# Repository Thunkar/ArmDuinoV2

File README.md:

# ArmDuinoV2
Second version of the robotic arm. Now including hardware, software and (some) documentation.

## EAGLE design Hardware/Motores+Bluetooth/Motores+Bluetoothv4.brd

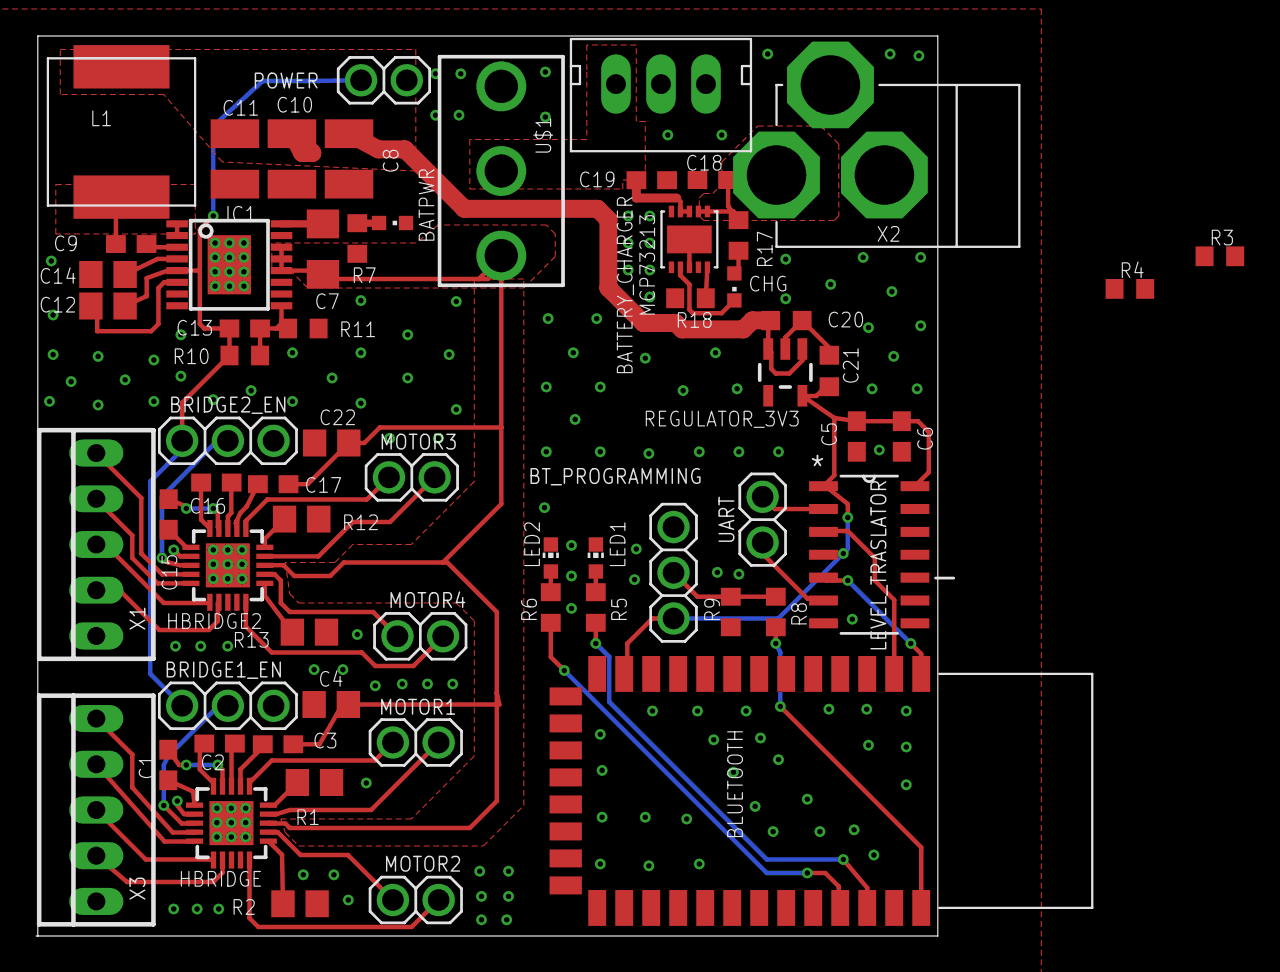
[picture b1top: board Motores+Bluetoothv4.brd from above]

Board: 2 copper layers, 50.0 x 50.0 mm, 63 parts (0 on the bottom side), 56 nets.

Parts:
BATPWR: CHIPLED_0603
BATTERY_CHARGER: MCP73213; DFN103X3
BLUETOOTH: HC_05; BLUETOOTH_SMD
BRIDGE1_EN, BRIDGE2_EN: 1X03ROUND
BT_PROGRAMMING: 1X03ROUND
C1, C2, C3, C5, C6, C15, C16, C17: 100n; C0603
C4, C22: 10uF; C0805
C7: 10u; C1206
C8, C10, C11: 47uF; C1210
C9: 470n; C0603
C12: 1uF; C0805
C13: 44pF; C0603
C14: 2.2uF; C0805
C18, C19: 1u; C0603
C20, C21: 2.2u; C0603K
CHG: CHIPLED_0603
HBRIDGE, HBRIDGE2: A3906; QFN20
IC1: LM43603; PW_R-PDSO-G16
L1: IHLP-3232DZ-01
LED1, LED2: CHIP-LED0603
LEVEL_TRASLATOR: 74LCX125M; SOIC127P600X175-14N
MOTOR1, MOTOR2, MOTOR3, MOTOR4: 1X02ROUND
POWER: 1X02ROUND
R1, R2, R12, R13: 0R2; R0805
R3: R0603
R4: NM; R0603
R5, R6: 470; R0603
R7, R17, R18: 2k2; R0603
R8: 1k; R0603
R9: 10k; R0603
R10: 249k; R0603
R11: 63k; R0603
REGULATOR_3V3: V_REG_LDOSMD; SOT23-5
U$1: 100SP1T1B4M2QE
U$3: JST-XHA-3
UART: 1X02ROUND
X1, X3: 22-23-2051
X2: DC21MMX; DC-21MM

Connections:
3V3: BLUETOOTH.12, BT_PROGRAMMING.3, C5.2, C6.1, C21.1, LEVEL_TRASLATOR.1, LEVEL_TRASLATOR.4, LEVEL_TRASLATOR.14, REGULATOR_3V3.5
+5V: BRIDGE1_EN.3, BRIDGE2_EN.3, C8.1, C10.1, C11.1, C12.1, C13.1, C20.1, IC1.5, L1.P$2, POWER.1, R10.2, REGULATOR_3V3.1, REGULATOR_3V3.3
+5VRAW: BATTERY_CHARGER.P$1, BATTERY_CHARGER.P$2, C18.1, R17.2, X2.2
BT_PROG: BT_PROGRAMMING.2, R8.1, R9.2
BT_PROG_PIN: BLUETOOTH.34, R8.2
GND: BATPWR.C, BATTERY_CHARGER.P$8, BATTERY_CHARGER.P$9, BATTERY_CHARGER.P$11, BLUETOOTH.13, BLUETOOTH.21, BLUETOOTH.22, BRIDGE1_EN.1, BRIDGE2_EN.1, BT_PROGRAMMING.1, C4.1, C5.1, C6.2, C7.1, C8.2, C10.2, C11.2, C12.2, C14.2, C18.2, C19.2, C20.2, C21.2, C22.1, HBRIDGE.2, HBRIDGE.EXP, HBRIDGE2.2, HBRIDGE2.EXP, IC1.6, IC1.10, IC1.15, IC1.16, IC1.TP, LED1.C, LED2.C, LEVEL_TRASLATOR.7, LEVEL_TRASLATOR.10, LEVEL_TRASLATOR.13, POWER.2, R1.1, R2.1, R9.1, R11.1, R12.1, R13.1, R18.1, REGULATOR_3V3.2, U$1.1, U$3.P$1, X1.1, X2.1, X2.3, X3.1
LED1: BLUETOOTH.32, R5.2
LED2: BLUETOOTH.31, R6.2
unnamed: C1.1, HBRIDGE.19
unnamed: C1.2, HBRIDGE.1
unnamed: C2.1, HBRIDGE.18
unnamed: C2.2, HBRIDGE.20
unnamed: C3.2, HBRIDGE.17
unnamed: LED2.A, R6.1
unnamed: HBRIDGE.15, R1.2
unnamed: HBRIDGE.11, R2.2
unnamed: HBRIDGE.4, X3.5
unnamed: HBRIDGE.5, X3.4
unnamed: HBRIDGE.6, X3.3
unnamed: HBRIDGE.7, X3.2
unnamed: BRIDGE1_EN.2, HBRIDGE.3
unnamed: LED1.A, R5.1
unnamed: BATPWR.A, R7.2
unnamed: C9.2, IC1.3
unnamed: C9.1, IC1.1, IC1.2, L1.P$1
unnamed: C14.1, IC1.4
unnamed: C13.2, IC1.9, R10.1, R11.2
unnamed: C15.1, HBRIDGE2.19
unnamed: C15.2, HBRIDGE2.1
unnamed: C16.1, HBRIDGE2.18
unnamed: C16.2, HBRIDGE2.20
unnamed: C17.2, HBRIDGE2.17
unnamed: HBRIDGE2.15, R12.2
unnamed: HBRIDGE2.11, R13.2
unnamed: HBRIDGE2.4, X1.5
unnamed: HBRIDGE2.5, X1.4
unnamed: HBRIDGE2.6, X1.3
unnamed: HBRIDGE2.7, X1.2
unnamed: BRIDGE2_EN.2, HBRIDGE2.3
unnamed: CHG.A, R17.1
unnamed: BATTERY_CHARGER.P$7, CHG.C
unnamed: BATTERY_CHARGER.P$10, R18.2
OUT1A: HBRIDGE.16, MOTOR1.1
OUT1B: HBRIDGE.14, MOTOR1.2
OUT2A: HBRIDGE.10, MOTOR2.1
OUT2B: HBRIDGE.12, MOTOR2.2
OUT3A: HBRIDGE2.16, MOTOR3.1
OUT3B: HBRIDGE2.14, MOTOR3.2
OUT4A: HBRIDGE2.10, MOTOR4.1
OUT4B: HBRIDGE2.12, MOTOR4.2
RX_ARM: LEVEL_TRASLATOR.6, UART.2
RX_BT: BLUETOOTH.2, LEVEL_TRASLATOR.3
TX_ARM: LEVEL_TRASLATOR.2, UART.1
TX_BT: BLUETOOTH.1, LEVEL_TRASLATOR.5
VBAT: BATTERY_CHARGER.P$3, BATTERY_CHARGER.P$4, C19.1, U$1.2, U$3.P$3
VBB: C3.1, C4.2, C7.2, C17.1, C22.2, HBRIDGE.13, HBRIDGE2.13, IC1.12, IC1.13, IC1.14, R7.1, U$1.3

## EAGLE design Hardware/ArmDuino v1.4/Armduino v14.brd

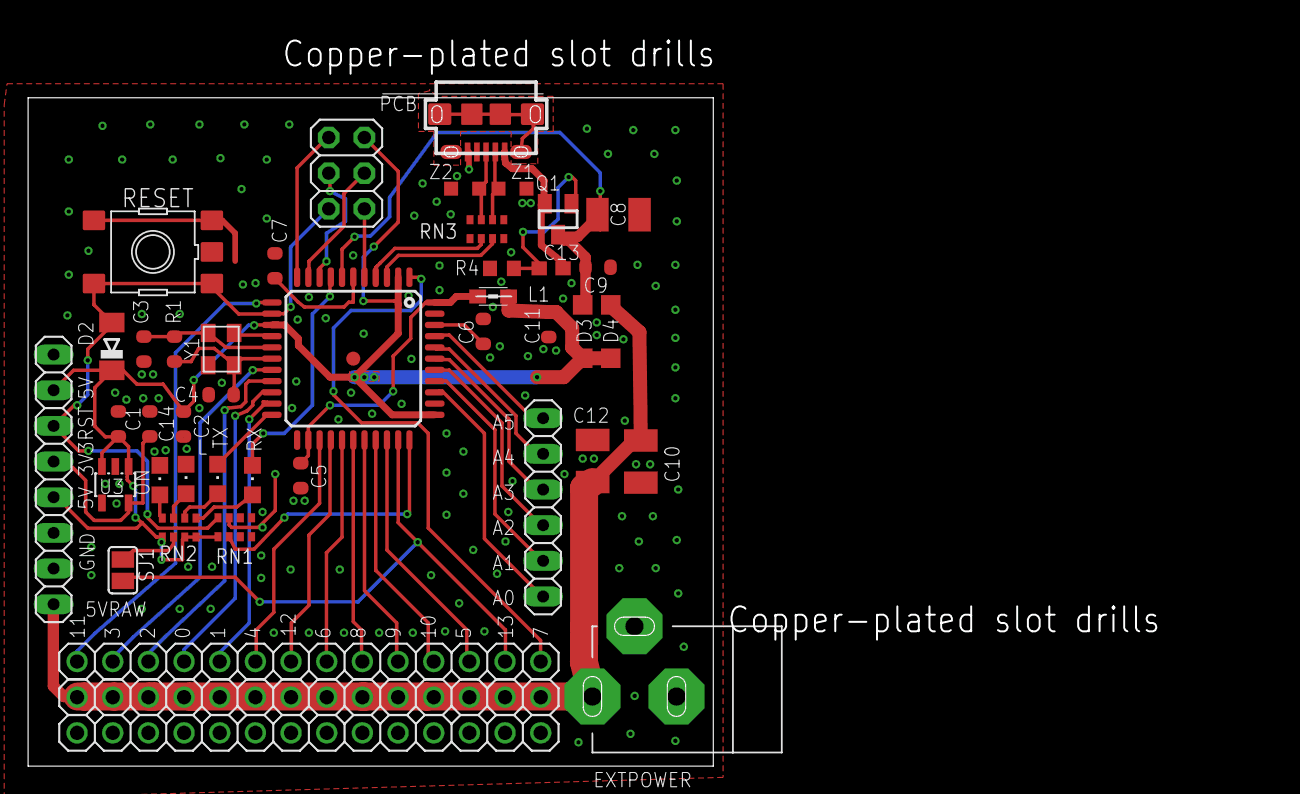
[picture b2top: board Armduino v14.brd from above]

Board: 2 copper layers, 48.8 x 47.6 mm, 43 parts (0 on the bottom side), 49 nets.

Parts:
C1, C2, C6, C9: 100n; C0603-ROUND
C3, C4: 22p; C0603-ROUND
C5, C7: 1uF; C0603-ROUND
C8, C10, C12: 10u; SMC_B
C11, C14: 1u; C0603-ROUND
C13: 100n; C0603
D2: CD1206-S01575; MINIMELF
D3, D4: SOD123
EXTPOWER: SMARTPRJ_POWERSUPPLY_DC21MMX; SMARTPRJ_POWERSUPPLY_DC-21MM
ICSP: ICSP; 2X03
J1: USB MICRO; SMARTPRJ_CON2_USB_MICRO_B_AT
J3: 8x1F-H8.5; 1X08
J4: 6x1F-H8.5; 1X06
JP1, JP2, JP3: 1X14ROUND
L: Yellow; CHIPLED_0805
L1: MH2029-300Y; 0805
ON: Green; CHIPLED_0805
Q1: FDN360P; SUPER-SOT3
R1: 1M; R0603-ROUND
R4: 1k; R0603
RESET: TS42
RN1: 10K; CAY16
RN2: 1K; CAY16
RN3: 22R; CAY16
RX: Yellow; CHIPLED_0805
SJ1: SJ
TX: Yellow; CHIPLED_0805
U2: ATMEGA32U4-XUAU; TQFP44-PAD
U3: LP2985-33DBVR; SOT23-DBV
Y1: 16MHz KX-7; CRYSTAL-3.2-2.5
Z1, Z2: CG0603MLC-05E; CT/CN0603

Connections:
+3V3: C14.2, J3.4, U3.5
+5V: C1.1, C2.1, C11.2, D2.C, D3.C, D4.C, ICSP.2, J3.2, J3.5, L1.1, RN1.5, RN2.1, RN2.3, RN2.4, U2.2, U2.14, U2.34, U3.1, U3.3
+5VRAW: C10.+, C12.+, D4.A, EXTPOWER.2, J3.8, JP3.1, JP3.2, JP3.3, JP3.4, JP3.5, JP3.6, JP3.7, JP3.8, JP3.9, JP3.10, JP3.11, JP3.12, JP3.13, JP3.14
A0: J4.1, U2.36
A1: J4.2, U2.37
A2: J4.3, U2.38
A3: J4.4, U2.39
A4: J4.5, U2.40
A5: J4.6, U2.41
AREF: C6.2, U2.42
AVCC: C5.1, L1.2, U2.24, U2.44
D0/RX: JP2.4, U2.20
D1/TX: JP2.5, U2.21
D2/SDA: JP2.3, U2.19
D3/SCL: JP2.2, U2.18
D4: JP2.6, U2.25
D5*: JP2.12, U2.31
D6*: JP2.8, U2.27
D7: JP2.14, U2.1
D+: J1.P3, RN3.7, Z1.1
D-: J1.P2, RN3.6, Z2.1
GND: C1.2, C2.2, C3.1, C4.2, C5.2, C6.1, C7.2, C8.-, C9.1, C10.-, C11.1, C12.-, C14.1, EXTPOWER.1, EXTPOWER.3, ICSP.6, J1.P5, J3.6, J3.7, JP1.1, JP1.2, JP1.3, JP1.4, JP1.5, JP1.6, JP1.7, JP1.8, JP1.9, JP1.10, JP1.11, JP1.12, JP1.13, JP1.14, L.C, ON.C, R4.1, RESET.3, RESET.4, RN1.3, U2.5, U2.15, U2.23, U2.35, U2.43, U2.P$1, U3.2, Y1.2, Y1.4, Z1.2, Z2.2
HWB: RN1.6, U2.33
IO8: JP2.9, U2.28
IO9*: JP2.10, U2.29
IO10*: JP2.11, U2.30
IO11*: JP2.1, U2.12
IO12: JP2.7, U2.26
IO13*: JP2.13, SJ1.2, U2.32
LL: RN2.2, SJ1.1
MISO: ICSP.1, U2.11
MOSI: ICSP.4, U2.10
unnamed: C13.1, Q1.1, R4.2
unnamed: L.A, RN2.7
unnamed: ON.A, RN2.8
unnamed: J1.S1, J1.S2, J1.S3, J1.S4, J1.S5, J1.S6
unnamed: RN2.6, TX.A
unnamed: RN2.5, RX.A
RD+: RN3.2, U2.4
RD-: RN3.3, U2.3
RESET: D2.A, ICSP.5, J3.3, RESET.1, RESET.2, RN1.4, U2.13
RXLED: RX.C, U2.8
SCK: ICSP.3, U2.9
TXLED: TX.C, U2.22
UCAP: C7.1, U2.6
VUSB: C8.+, C9.2, D3.A, Q1.3, U2.7
VUSBRAW: C13.2, J1.P1, Q1.2
XTAL1: C4.1, R1.1, U2.17, Y1.1
XTAL2: C3.2, R1.2, U2.16, Y1.3

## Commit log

2015-02-18 Initial build
2015-02-22 Added voice control and commander. It works but it is seriously ugly u.u
2015-02-23 Added voice control commands and automatic tab switching.
2015-02-23 Some bugfixes
2015-02-26 Changed voice recognition thresholds.
2015-02-27 Fixing bugs before the presentation at the dotNETConference like a boss.
2015-02-28 Fixed project structure and added software and documentation. Thanks, #dotNETconference! ^^
2015-03-04 Added dependencies as part of the project and command example file.
2015-03-13 Removed unused tab.
2015-03-13 Uploaded Kinect dependencies.
2015-03-13 Added initial rover support.
2015-03-13 improved firmware
2015-03-13 Fixed library for Java 8. Now it needs a command line argument to be launched, gotta fix that.
2015-03-17 Updated with webcam and gamepad support.
2015-03-18 Updated TCP timing.
2015-03-18 updated with field enabling
2015-03-18 Bugfixed and refactored
2015-03-18 Moar bugfix
2015-03-20 Fixed CLI and added multiple client support.
2015-03-20 Fixed firmware bug.
2015-03-23 Added android software to ArmduinoV2 repository
2015-03-23 More files
2015-03-23 Added comments
2015-03-23 Added comments to firmware
2015-03-23 Removed unnecessary files and commented code.
2015-03-23 Fixed structure.
2015-03-23 Added CLI documentation.
2015-04-06 Fixed some bugs and added bluetooth support.
2015-04-07 Removed usage of pin13
2015-04-07 Minor changes to the view logic.
2015-04-10 Added rover control to the C# app and prepared firmware for bluetooth and TCP concurrent connections.
2015-04-11 Added diferential turn and reset movement button.
2015-04-15 Added sensor reading capabilities.
2015-04-15 Fixed battery data parsing.
2015-04-15 Last minute bullshit
2015-04-15 Minor aesthetical changes
2015-04-15 Removed library search from in-app
2015-04-16 Try/catched some shit.
2015-04-28 Removed some commented code.
2015-04-29 Using proper JAVA_HOME now
2015-04-29 Modified CLI to support ACK and some renaming
2015-04-30 Some renaming
2015-05-11 Updated CLI to work with ROS.
2015-05-14 Added twist to navigation and removed legacy webcam streaming
2015-05-25 Fixed gitignore
